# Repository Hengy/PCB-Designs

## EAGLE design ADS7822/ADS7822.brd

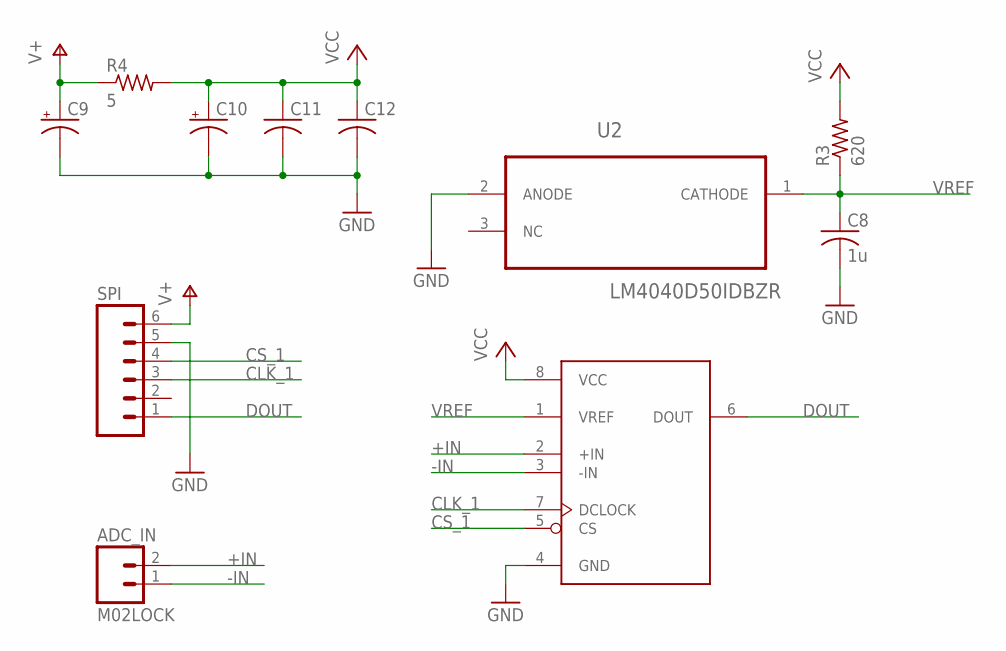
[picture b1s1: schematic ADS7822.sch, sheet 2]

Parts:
ADC_IN: M02LOCK; 1X02_LOCK
C8: 1u; C0805
C9, C10: CPOL-US; SMD_6.6X6.6
C11, C12: C-USC0805; C0805
R3: 620; R0805
R4: 5; R1206
SPI: M06LOCK; 1X06_LOCK
U2: LM4040D50IDBZR; SOT95P237X112-3N
U$3: ADS7822; SO-08

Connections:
+IN: ADC_IN.2, U$3.2 (+IN)
-IN: ADC_IN.1, U$3.3 (-IN)
CLK_1: SPI.3, U$3.7 (DCLOCK)
CS_1: SPI.4, U$3.5 (CS)
DOUT: SPI.1, U$3.6 (DOUT)
GND: C8.2, C9.-, C10.-, C11.2, C12.2, SPI.5, U2.2 (ANODE), U$3.4 (GND)
V+: C9.+, R4.1, SPI.6
VCC: C10.+, C11.1, C12.1, R3.2, R4.2, U$3.8 (VCC)
VREF: C8.1, R3.1, U2.1 (CATHODE), U$3.1 (VREF)

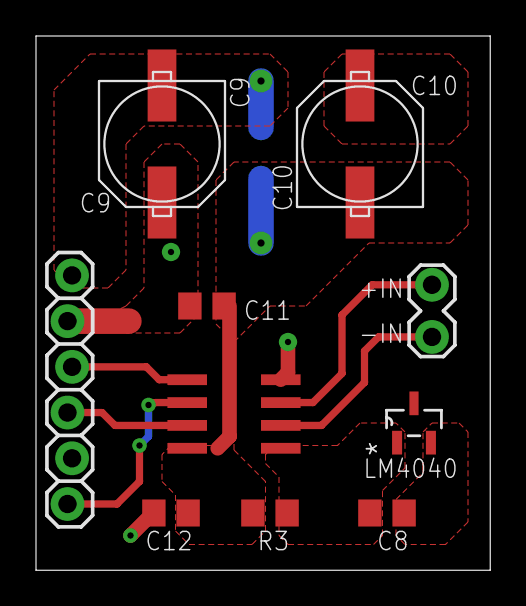
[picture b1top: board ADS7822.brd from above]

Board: 2 copper layers, 25.2 x 29.7 mm, 11 parts (1 on the bottom side), 9 nets.

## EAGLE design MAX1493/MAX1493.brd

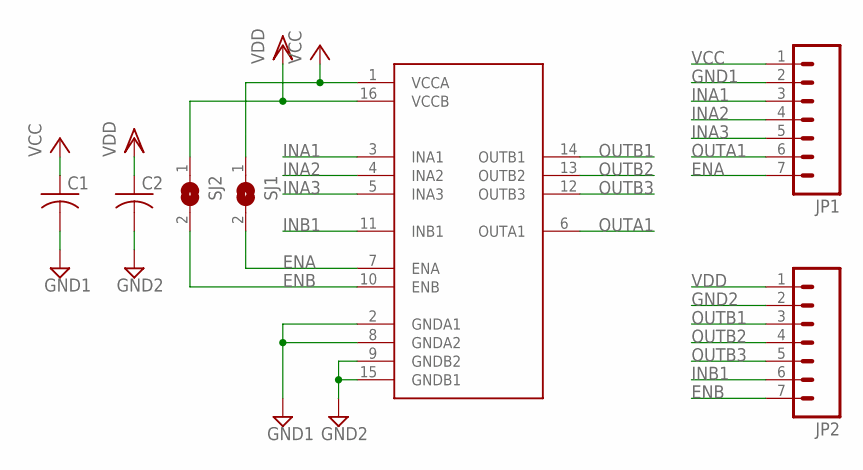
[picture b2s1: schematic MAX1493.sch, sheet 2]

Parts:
C1, C2: C-USC0805; C0805
JP1, JP2: M07LOCK; 1X07_LOCK
SJ1, SJ2: SJ
U$1: MAX14931; SO16

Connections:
ENA: JP1.7, SJ1.2, U$1.7 (ENA)
ENB: JP2.7, SJ2.2, U$1.10 (ENB)
GND1: C1.2, JP1.2, U$1.2 (GNDA1), U$1.8 (GNDA2)
GND2: C2.2, JP2.2, U$1.9 (GNDB2), U$1.15 (GNDB1)
INA1: JP1.3, U$1.3 (INA1)
INA2: JP1.4, U$1.4 (INA2)
INA3: JP1.5, U$1.5 (INA3)
INB1: JP2.6, U$1.11 (INB1)
OUTA1: JP1.6, U$1.6 (OUTA1)
OUTB1: JP2.3, U$1.14 (OUTB1)
OUTB2: JP2.4, U$1.13 (OUTB2)
OUTB3: JP2.5, U$1.12 (OUTB3)
VCC: C1.1, JP1.1, SJ1.1, U$1.1 (VCCA)
VDD: C2.1, JP2.1, SJ2.1, U$1.16 (VCCB)

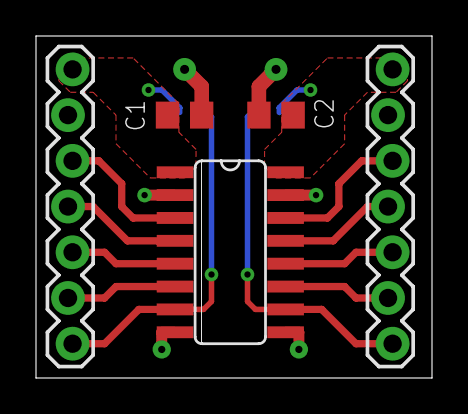
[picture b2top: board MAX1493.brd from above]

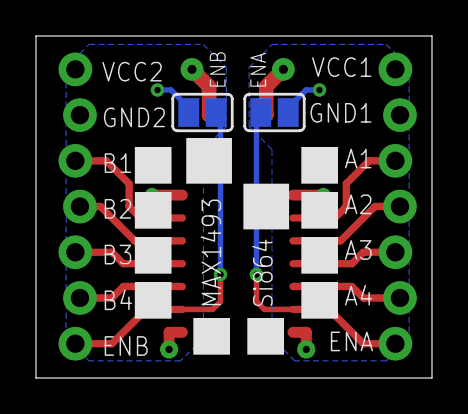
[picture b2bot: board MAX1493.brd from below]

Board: 2 copper layers, 22.0 x 19.0 mm, 7 parts (2 on the bottom side), 14 nets.

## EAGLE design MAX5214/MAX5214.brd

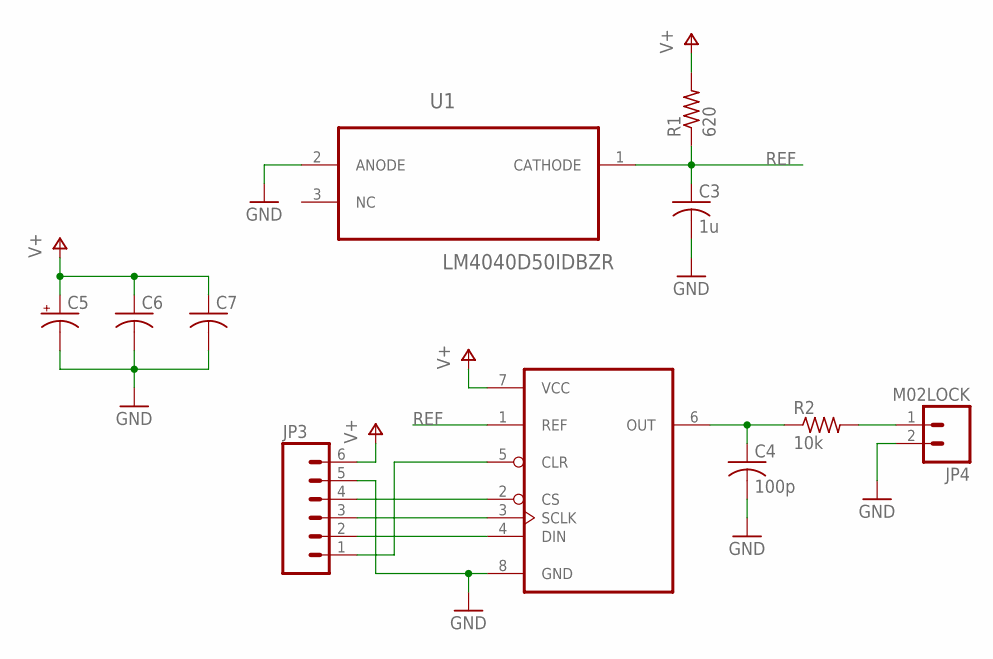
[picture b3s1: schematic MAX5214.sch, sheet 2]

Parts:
C3: 1u; C0805
C4: 100p; C0805
C5: CPOL-US; SMD_6.6X6.6
C6, C7: C-USC0805; C0805
JP3: M06LOCK; 1X06_LOCK
JP4: M02LOCK; 1X02_LOCK
R1: 620; R0805
R2: 10k; R0805
U1: LM4040D50IDBZR; SOT95P237X112-3N
U$2: MAX5214; UMAX8

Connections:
CLR: JP3.1, U$2.5 (CLR)
CS: JP3.4, U$2.2 (CS)
DIN: JP3.2, U$2.4 (DIN)
GND: C3.2, C4.2, C5.-, C6.2, C7.2, JP3.5, JP4.2, U1.2 (ANODE), U$2.8 (GND)
unnamed: JP4.1, R2.2
unnamed: C4.1, R2.1, U$2.6 (OUT)
REF: C3.1, R1.1, U1.1 (CATHODE), U$2.1 (REF)
SCLK: JP3.3, U$2.3 (SCLK)
V+: C5.+, C6.1, C7.1, JP3.6, R1.2, U$2.7 (VCC)

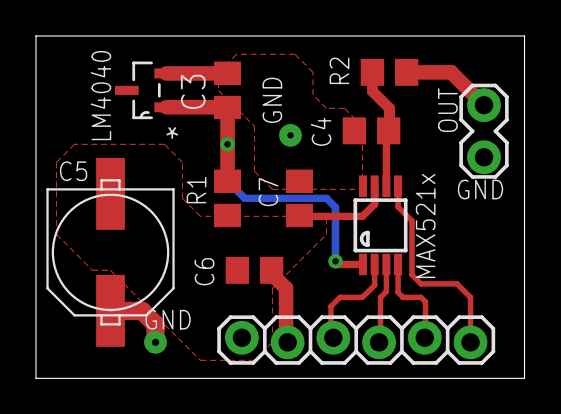
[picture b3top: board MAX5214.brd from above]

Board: 2 copper layers, 27.1 x 19.0 mm, 11 parts (0 on the bottom side), 9 nets.

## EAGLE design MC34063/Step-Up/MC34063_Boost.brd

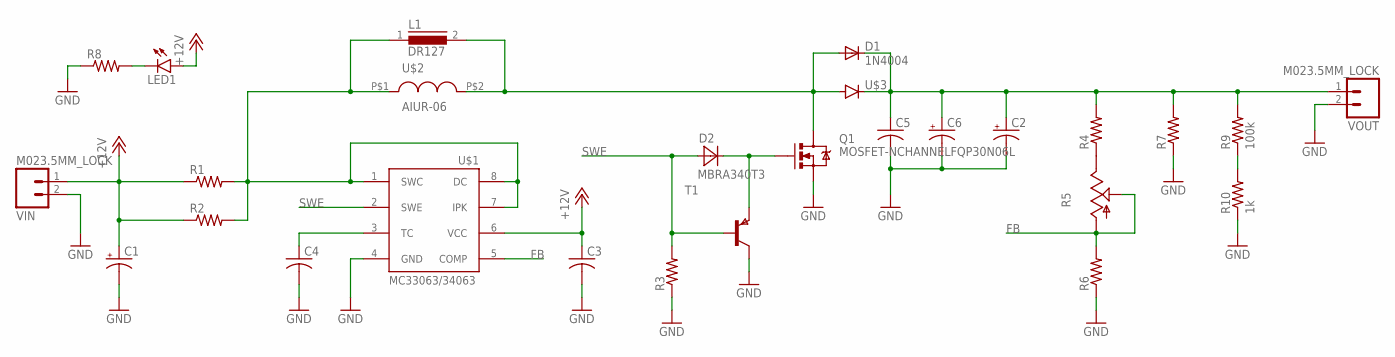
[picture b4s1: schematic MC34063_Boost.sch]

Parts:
C1, C6: CPOL-USE3.5-8; E3,5-8
C2: CPOL-USE2.5-6; E2,5-6
C3: C-USC0805K; C0805K
C4: C-USC0805; C0805
C5: C-USC1206; C1206
D1: 1N4004; DO41-10
D2: MBRA340T3; SMA
L1: DR127
LED1: LED1206; LED-1206
Q1: MOSFET-NCHANNELFQP30N06L; TO220V
R1, R2: R-US_R1206; R1206
R3, R4, R6, R7, R8: R-US_R0805; R0805
R5: TRIM_US-S64W; S64W
R9: 100k; R0805
R10: 1k; R0805
T1: PNPSOT223; SOT223
U$1: MC33063/MC34063D; SO08
U$2: AIUR-06; 7MM_LEADS_12MM
U$3: DIODESMA; SMA-DIODE
VIN: M023.5MM_LOCK; SCREWTERMINAL-3.5MM-2_LOCK
VOUT: M023.5MM_LOCK; SCREWTERMINAL-3.5MM-2_LOCK

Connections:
+12V: C1.+, C3.1, LED1.A, R1.1, R2.1, U$1.6 (VCC), VIN.1
FB: R5.A, R5.S, R6.2, U$1.5 (COMP)
GND: C1.-, C2.-, C3.2, C4.2, C5.2, C6.-, Q1.3 (S), R3.1, R6.1, R7.1, R8.1, R10.1, T1.2 (C), T1.4 (C), U$1.4 (GND), VIN.2, VOUT.2
HIGHV: C2.+, C5.1, C6.+, D1.C, R4.2, R7.2, R9.2, U$3.C, VOUT.1
unnamed: C4.1, U$1.3 (TC)
unnamed: L1.1, R1.2, R2.2, U$1.1 (SWC), U$1.7 (IPK), U$1.8 (DC), U$2.P$1 (1)
unnamed: D1.A, L1.2, Q1.2 (D), U$2.P$2 (2), U$3.A
unnamed: LED1.C, R8.2
unnamed: R4.1, R5.E
unnamed: D2.C, Q1.1 (G), T1.3 (E)
SWE: D2.A, R3.2, T1.1 (B), U$1.2 (SWE)
TEST: R9.1, R10.2

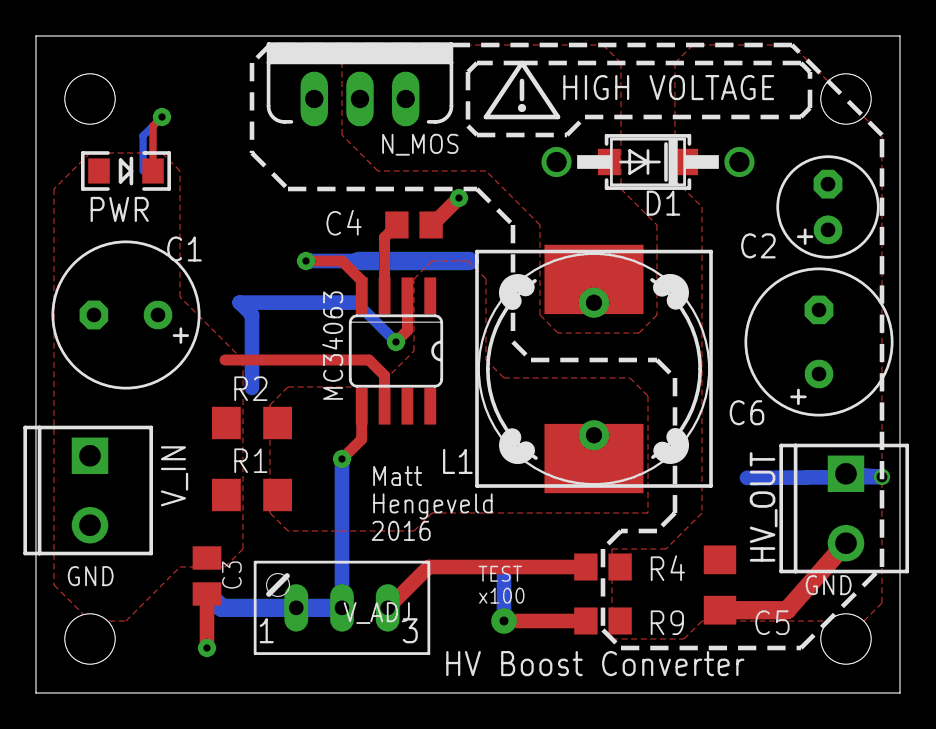
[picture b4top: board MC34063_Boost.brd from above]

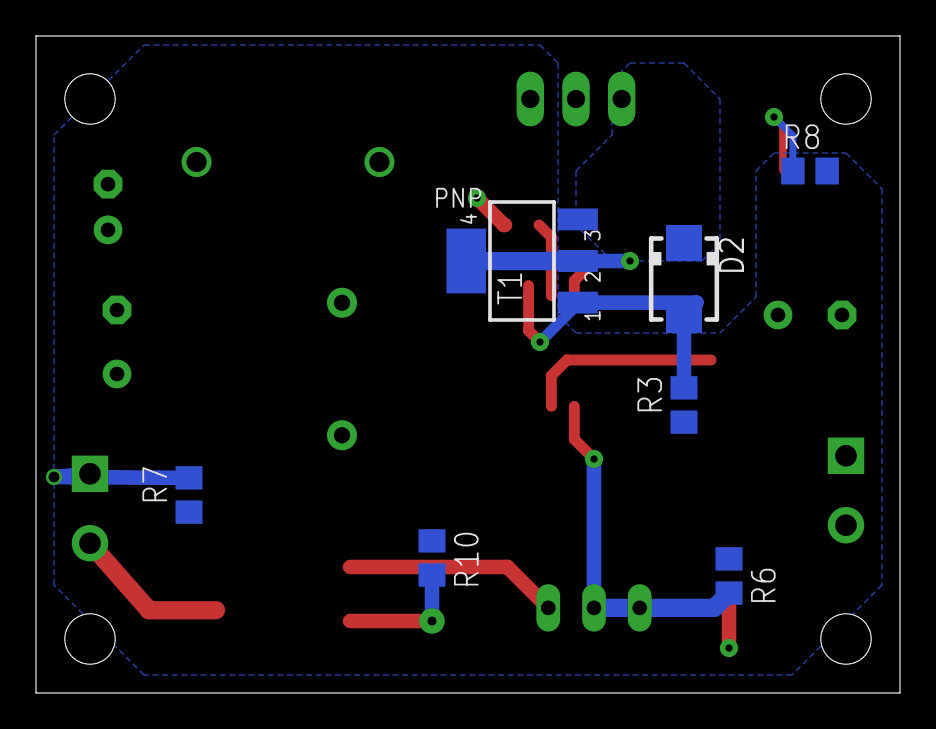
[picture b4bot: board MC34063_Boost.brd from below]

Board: 2 copper layers, 48.0 x 36.5 mm, 27 parts (7 on the bottom side), 12 nets.

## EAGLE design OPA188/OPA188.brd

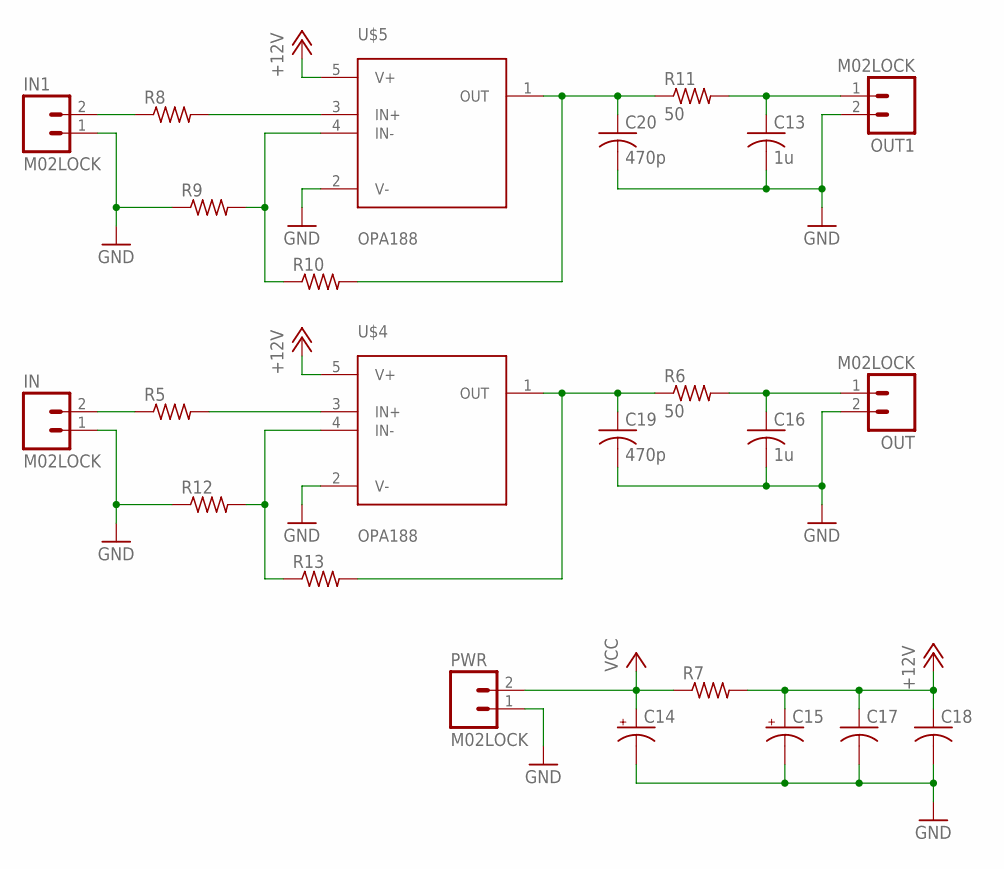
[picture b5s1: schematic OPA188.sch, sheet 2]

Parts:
C13, C16: 1u; C0805
C14, C15: CPOL-US; SMD_6.6X6.6
C17, C18: C-USC0805; C0805
C19, C20: 470p; C0805
IN, IN1: M02LOCK; 1X02_LOCK
OUT, OUT1: M02LOCK; 1X02_LOCK
PWR: M02LOCK; 1X02_LOCK
R5, R8, R9, R10, R12, R13: R-US_R0805; R0805
R6, R11: 50; R0805
R7: R-US_R1206; R1206
U$4, U$5: OPA188; SOT23-DBV

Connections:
+12V: C15.+, C17.1, C18.1, R7.2, U$4.5 (V+), U$5.5 (V+)
GND: C13.2, C14.-, C15.-, C16.2, C17.2, C18.2, C19.2, C20.2, IN.1, IN1.1, OUT.2, OUT1.2, PWR.1, R9.1, R12.1, U$4.2 (V-), U$5.2 (V-)
unnamed: C16.1, OUT.1, R6.2
unnamed: IN1.2, R8.1
unnamed: IN.2, R5.1
unnamed: R5.2, U$4.3 (IN+)
unnamed: R8.2, U$5.3 (IN+)
unnamed: R12.2, R13.1, U$4.4 (IN-)
unnamed: C19.1, R6.1, R13.2, U$4.1 (OUT)
unnamed: R9.2, R10.1, U$5.4 (IN-)
unnamed: C20.1, R10.2, R11.1, U$5.1 (OUT)
unnamed: C13.1, OUT1.1, R11.2
VCC: C14.+, PWR.2, R7.1

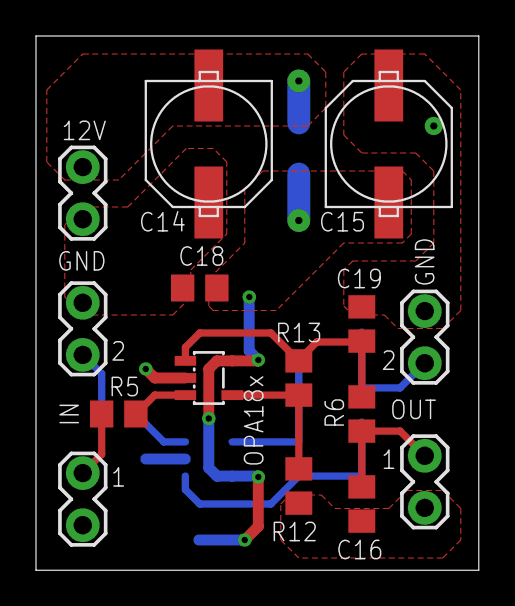
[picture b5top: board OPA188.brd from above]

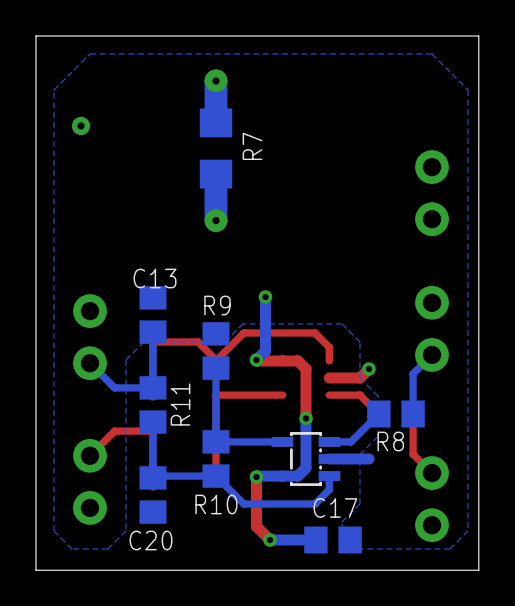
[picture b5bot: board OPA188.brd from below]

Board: 2 copper layers, 24.6 x 29.7 mm, 24 parts (9 on the bottom side), 13 nets.

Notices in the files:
parts and their libraries:
SparkFun-Connectors: Licensing: Creative Commons ShareAlike 4.0 International - https://creativecommons.org/licenses/by-sa/4.0
